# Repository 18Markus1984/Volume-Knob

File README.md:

# Volume Knob V2 (USB-C)

A compact USB volume knob based on an **Arduino Pro Micro (USB-C)**. Turn it to change your computer's volume, click to mute – and eight RGB LEDs under a transparent ring give visual feedback with selectable colors and animations.

The knob shows up as a standard USB media keyboard, so it works on Windows, macOS and Linux without any drivers.

**3D-printable parts, photos and more:** [Printables – Volume Knob V2 (USB-C)](https://www.printables.com/model/154855-volume-knob-v2-usb-c)

---

## Features

- Volume up / down by turning the knob, mute by clicking it
- 8 addressable RGB LEDs (SK6812) behind a clear printed ring
- 25 selectable colors
- Several LED animation modes
- Color and mode are stored in EEPROM and survive unplugging
- USB-C, plug & play (USB HID consumer control)
- Roughly **€20** in parts per knob

## Bill of Materials

| Qty | Part | Notes |
|---:|---|---|
| 1 | Arduino Pro Micro (ATmega32U4, **USB-C**) | 5 V / 16 MHz |
| 8 | SK6812 RGB LED, 5050 package | WS2812B-compatible |
| 1 | ALPS rotary encoder with push switch | |
| 1 | 10 kΩ resistor | |
| 1 | Custom PCB | KiCad project and Gerbers in this repo |
| 4 | M3 × 16 screws | |
| 4 | M3 threaded inserts | |
| – | PLA + clear/transparent filament | for the housing and the light ring |

## 3D Printing

All parts print fine in **PLA**. Print the **light ring in transparent filament** so the LEDs shine through. The bottom can optionally be printed with a decorative pattern – an *Octagram Spiral* top/bottom surface pattern looks great.

The print files are on [Printables](https://www.printables.com/model/154855-volume-knob-v2-usb-c); the source CAD files (Autodesk Inventor, STEP, STL) are in [`ProMicroKiCad-master/VolumeKnob/3DObjekt`](ProMicroKiCad-master/VolumeKnob/3DObjekt).

## Assembly

1. Solder the rotary encoder, the Arduino Pro Micro and the resistor onto the PCB.
2. Melt the four M3 threaded inserts into the holes of the bottom housing.
3. Snap the transparent ring into the housing (snap-fit, no glue needed).
4. Fasten the PCB assembly with the four M3 screws.
5. Press the knob onto the encoder shaft – it's a press fit, no adhesive required.

## Wiring

| Pro Micro pin | Connected to |
|---:|---|
| 7 | LED data in (SK6812 chain) |
| 6 | Encoder CLK (A) |
| 5 | Encoder DT (B) |
| 2 | Encoder push button (SW) |

## Firmware

The sketch is located at [`volumeKnob/volumeKnob.ino`](volumeKnob/volumeKnob.ino).

### Required libraries

Install via the Arduino Library Manager:

- [HID-Project](https://github.com/NicoHood/HID) by NicoHood – USB media keys
- [Encoder](https://github.com/PaulStoffregen/Encoder) by Paul Stoffregen
- [Adafruit NeoPixel](https://github.com/adafruit/Adafruit_NeoPixel)
- [OneButton](https://github.com/mathertel/OneButton) by Matthias Hertel
- EEPROM (included with the Arduino IDE)

### Upload

1. Select the board **Arduino Leonardo** (or *SparkFun Pro Micro, 5 V / 16 MHz* if you have the SparkFun board package installed).
2. Choose the correct port and upload.

If you use a different number of LEDs, change `NUMPIXELS` at the top of the sketch.

> **Note:** On startup the knob sends 50× *Volume Down* followed by 2× *Volume Up*, so your system volume is set to a low, known level every time it is plugged in.

## Usage

| Action | Volume mode | Color menu | Mode menu |
|---|---|---|---|
| **Turn** | Volume up / down | Browse the 25 colors | Browse the animation modes |
| **Click** | Mute / unmute | Save color & go back | Save mode & go back |
| **Long press** | Open color menu | Open mode menu | Back to volume mode (without saving) |

Two encoder detents equal one volume step.

### LED modes

- **Single pixel** – one LED follows the knob and slowly fades out
- **Rainbow fade** – all LEDs fade through the color wheel
- **Rainbow wheel** – a rotating rainbow around the ring
- **Pixel trail** – three LEDs follow the knob and stay lit

In the mode menu the modes are arranged in groups around the ring, separated by a dark position.

## Repository Structure

```
Volume-Knob/
├── volumeKnob/volumeKnob.ino          # current firmware (V2)
├── images/                            # photos and GIFs
└── ProMicroKiCad-master/
    ├── VolumeKnob/
    │   ├── VolumeKnob.kicad_pro/_sch/_pcb   # KiCad project of the PCB
    │   ├── jlcpcb/                     # Gerber, BOM & CPL for JLCPCB
    │   ├── Gerber/                     # older Gerber revisions
    │   ├── 3DObjekt/                   # Inventor / STEP / STL files
    │   └── Code/                       # older sketches and test code
    └── ProMicroKiCad-master/           # Pro Micro KiCad library
```

## Gallery

## Version 1

The first version used a micro-USB Pro Micro, single-color green LEDs and a hand-wired build (8× green LEDs, 2× 10 kΩ resistors). Using individual LEDs instead of a ring PCB wasn't the best idea – it took some hot glue to hold everything in place – which led to the V2 with a custom PCB, RGB LEDs and USB-C.

---

Made by **Max Siebenschläfer** – find more projects on [Printables](https://www.printables.com/model/154855-volume-knob-v2-usb-c).

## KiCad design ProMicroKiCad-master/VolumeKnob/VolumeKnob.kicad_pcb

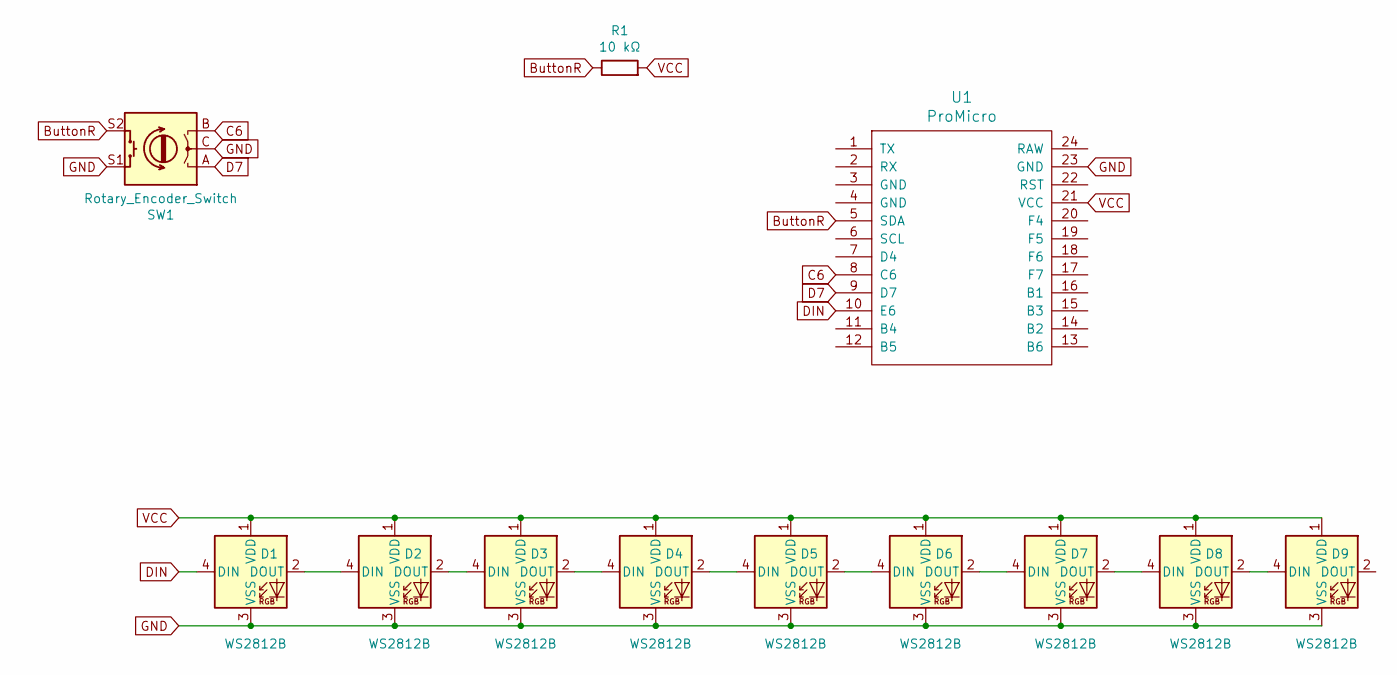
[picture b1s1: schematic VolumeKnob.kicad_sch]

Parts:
D1, D2, D3, D4, D5, D6, D7, D8, D9: WS2812B; LED_WS2812B_PLCC4_5.0x5.0mm_P3.2mm; LCSC C114586
R1: 10 kΩ; R_Axial_DIN0207_L6.3mm_D2.5mm_P10.16mm_Horizontal
SW1: Rotary_Encoder_Switch; RotaryEncoder_Alps_EC12E-Switch_Vertical_H20mm
U1: ProMicro; ProMicro-NoSilk

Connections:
ButtonR: R1.1, SW1.S2, U1.5 (SDA)
C6: SW1.B, U1.8 (C6)
D7: SW1.A, U1.9 (D7)
DIN: D1.4 (DIN), U1.10 (E6)
GND: D1.3 (VSS), D2.3 (VSS), D3.3 (VSS), D4.3 (VSS), D5.3 (VSS), D6.3 (VSS), D7.3 (VSS), D8.3 (VSS), D9.3 (VSS), SW1.C, SW1.S1, U1.23 (GND)
unnamed: D1.2 (DOUT), D2.4 (DIN)
unnamed: D2.2 (DOUT), D3.4 (DIN)
unnamed: D3.2 (DOUT), D4.4 (DIN)
unnamed: D4.2 (DOUT), D5.4 (DIN)
unnamed: D5.2 (DOUT), D6.4 (DIN)
unnamed: D6.2 (DOUT), D7.4 (DIN)
unnamed: D7.2 (DOUT), D8.4 (DIN)
unnamed: D8.2 (DOUT), D9.4 (DIN)
VCC: D1.1 (VDD), D2.1 (VDD), D3.1 (VDD), D4.1 (VDD), D5.1 (VDD), D6.1 (VDD), D7.1 (VDD), D8.1 (VDD), D9.1 (VDD), R1.2, U1.21 (VCC)

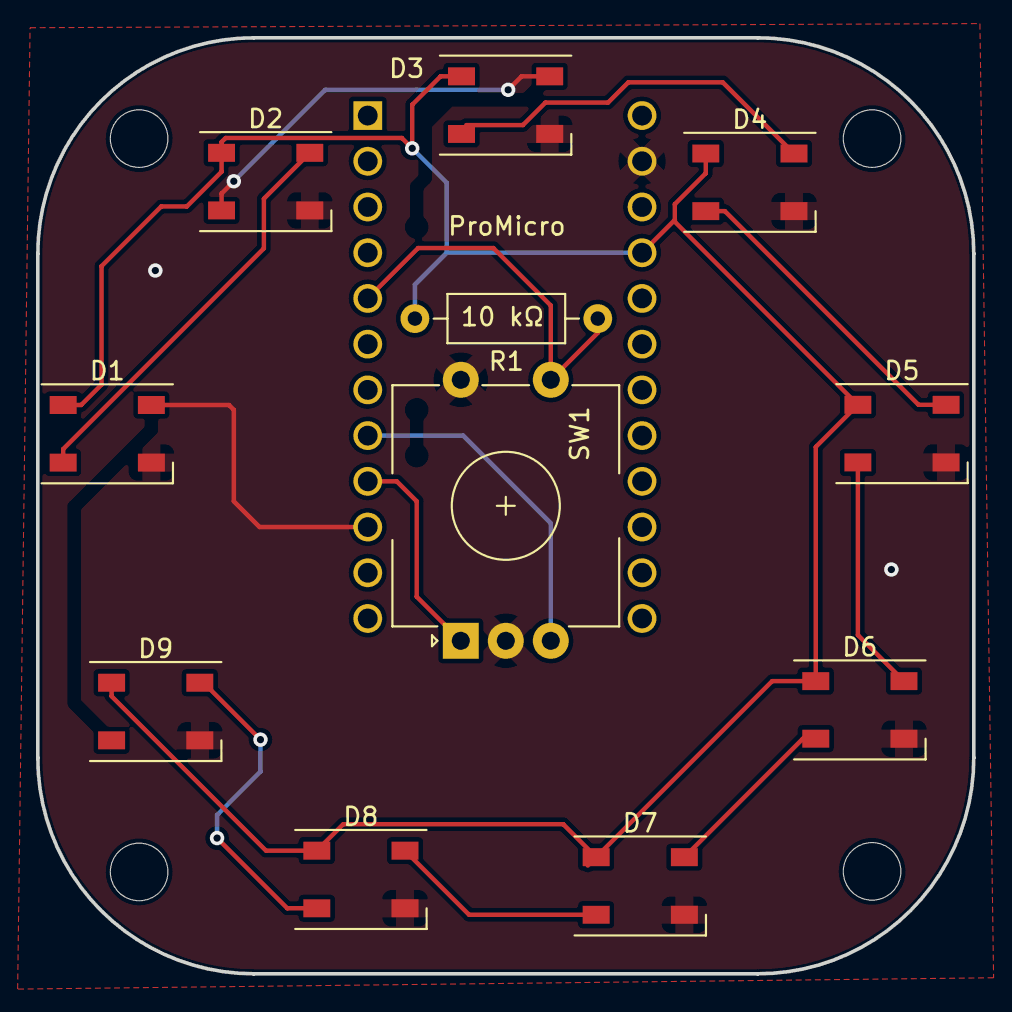
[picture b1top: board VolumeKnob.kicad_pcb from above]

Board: 2 copper layers, 52.0 x 52.0 mm, 12 parts (0 on the bottom side), 14 nets.

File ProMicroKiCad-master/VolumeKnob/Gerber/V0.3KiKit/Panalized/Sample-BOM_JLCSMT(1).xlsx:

Comment | Designator | Footprint | JLCPCB Part #（optional）
WS2812B | D1,D2,D3,D4,D5,D6,D7,D8,D9 | LED_SMD:LED_WS2812B_PLCC4_5.0x5.0mm_P3.2mm | C114586

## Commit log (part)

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2021-05-26 Create the file
2021-05-26 Create puffer
2021-05-26 images
2021-05-26 add the images
2021-11-28 Settings Menu
2021-12-14 Completly new structur
    The second version had all going and made it difficult to show rainbow colors with full controll of the button and the rotary encoder. I also tried pseudo "Threads", but they doesn't work and were he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
2021-12-14 images for V2
2021-12-17 Added Menu better controls
    You can chose a mode and many bugs are fixed. Two new modes with rainbow-colors.
2021-12-19 New Mode
    From 0 to 33 percent Volume the LEDs are green, from 34 till 66 the LEDs are yellow and the rest are red.
2021-12-19 New Mode
2021-12-19 Added a new mode
    You spin, 3 LEDs move and stay always on
2022-01-12 comments and some variables got better naming
2022-01-12 comments
2022-02-25 Changed PCB Layout // Changes to code
    Fixed static LED Numbers
2022-03-02 moved .ino file to an extra folder for arduino ide
2022-03-04 removed debug
2022-03-25 animation
2022-03-25 Added animation and a explosion image
2022-03-25 BetterAnimation
2022-03-25 MarketingMaterial
2022-03-25 New rotary knob with a Pause/Play symbol
2022-03-31 Create test
2022-03-31 Create VolumeKnob
2022-03-31 Rename VolumeKnob to VolumeKnob.ino
2022-03-31 updated images
